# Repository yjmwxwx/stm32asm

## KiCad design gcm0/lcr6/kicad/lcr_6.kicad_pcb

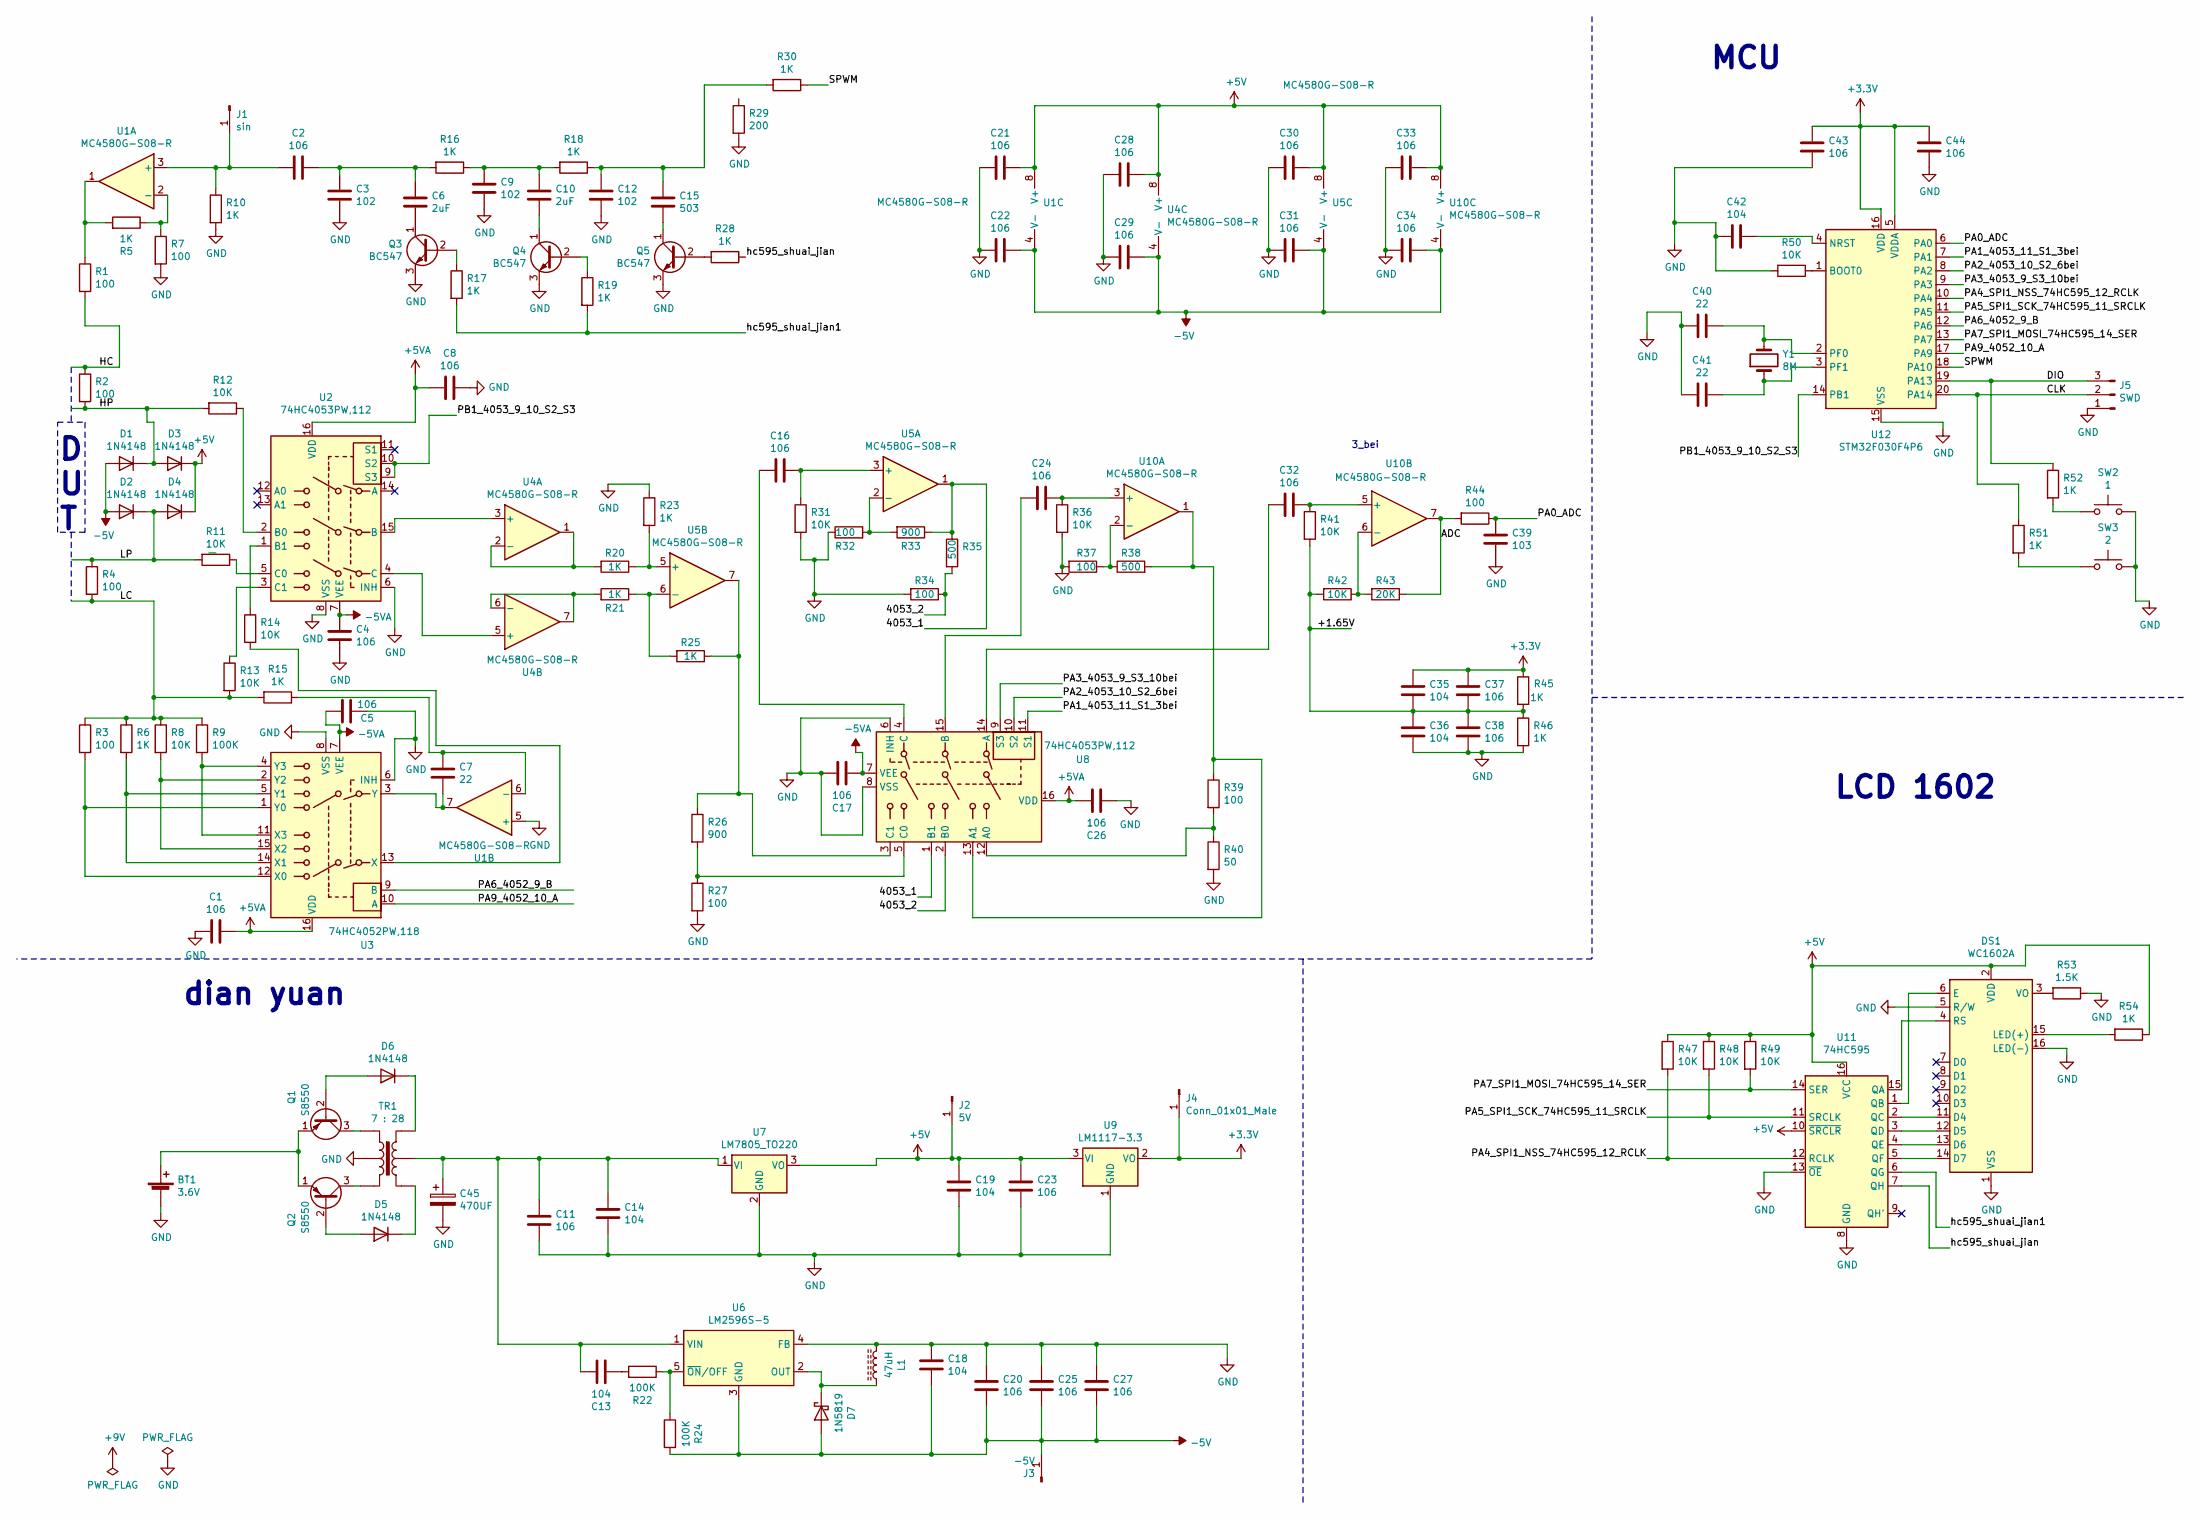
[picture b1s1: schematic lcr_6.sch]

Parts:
BT1: 3.6V; PinHeader_1x02_P2.54mm_Vertical
C1, C2, C4, C5, C8, C11, C16, C17, C20, C21, C22, C23, C24, C25, C26, C27, C28, C29, C30, C31, C32, C33, C34, C37, C38, C43, C44: 106; C_0805_2012Metric_Pad1.18x1.45mm_HandSolder
C3, C9, C12: 102; C_0805_2012Metric_Pad1.18x1.45mm_HandSolder
C6, C10: 2uF; C_0805_2012Metric_Pad1.18x1.45mm_HandSolder
C7, C40, C41: 22; C_0805_2012Metric_Pad1.18x1.45mm_HandSolder
C13, C14, C18, C19, C35, C36, C42: 104; C_0805_2012Metric_Pad1.18x1.45mm_HandSolder
C15: 503; C_0805_2012Metric_Pad1.18x1.45mm_HandSolder
C39: 103; C_0805_2012Metric_Pad1.18x1.45mm_HandSolder
C45: 470UF; CP_Radial_D8.0mm_P3.80mm
D1, D2, D3, D4: 1N4148; D_SMA
D5, D6: 1N4148; D_DO-35_SOD27_P7.62mm_Horizontal
D7: 1N5819; D_SMA
DS1: WC1602A; PinHeader_1x16_P2.54mm_Vertical
J1: sin; PinHeader_1x01_P2.54mm_Vertical
J2: 5V; PinHeader_1x01_P2.54mm_Vertical
J3: -5V; PinHeader_1x01_P2.54mm_Vertical
J4: Conn_01x01_Male; PinHeader_1x01_P2.54mm_Vertical
J5: SWD; PinHeader_1x03_P2.54mm_Vertical
L1: 47uH; L_Radial_D6.0mm_P4.00mm
Q1, Q2: S8550; TO-92_Inline
Q3, Q4, Q5: BC547; TO-92_Inline
R1, R2, R3, R4, R7, R27, R32, R34, R37, R39, R44: 100; R_0805_2012Metric_Pad1.20x1.40mm_HandSolder
R5, R6, R10, R15, R16, R17, R18, R19, R20, R21, R23, R25, R28, R30, R45, R46, R51, R52, R54: 1K; R_0805_2012Metric_Pad1.20x1.40mm_HandSolder
R8, R11, R12, R13, R14, R31, R36, R41, R42, R47, R48, R49, R50: 10K; R_0805_2012Metric_Pad1.20x1.40mm_HandSolder
R9, R22, R24: 100K; R_0805_2012Metric_Pad1.20x1.40mm_HandSolder
R26, R33: 900; R_0805_2012Metric_Pad1.20x1.40mm_HandSolder
R29: 200; R_0805_2012Metric_Pad1.20x1.40mm_HandSolder
R35, R38: 500; R_0805_2012Metric_Pad1.20x1.40mm_HandSolder
R40: 50; R_0805_2012Metric_Pad1.20x1.40mm_HandSolder
R43: 20K; R_0805_2012Metric_Pad1.20x1.40mm_HandSolder
R53: 1.5K; R_0805_2012Metric_Pad1.20x1.40mm_HandSolder
SW2: 1; SW_Tactile_SPST_Angled_PTS645Vx58-2LFS
SW3: 2; SW_Tactile_SPST_Angled_PTS645Vx58-2LFS
TR1: 7 : 28; Transformer_Toroid_Tapped_Horizontal_D9.0mm_Amidon-T30
U1, U4, U5, U10: MC4580G-S08-R; SOP-8_3.9x4.9mm_P1.27mm
U2, U8: 74HC4053PW,112; TSSOP-16_4.4x5mm_P0.65mm
U3: 74HC4052PW,118; TSSOP-16_4.4x5mm_P0.65mm
U6: LM2596S-5; TO-263-5_TabPin3
U7: LM7805_TO220; TO-263-2
U9: LM1117-3.3; SOT-223-3_TabPin2
U11: 74HC595; TSSOP-16_4.4x5mm_P0.65mm
U12: STM32F030F4P6; TSSOP-20_4.4x6.5mm_P0.65mm
Y1: 8M; Crystal_HC49-4H_Vertical

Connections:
+3V3: C35.1, C37.1, C43.1, C44.1, J4.1, R45.1, U9.2 (VO), U12.5 (VDDA), U12.16 (VDD)
+5V: C19.1, C21.1, C23.1, C28.1, C30.1, C33.1, D3.1 (K), D4.1 (K), DS1.2 (VDD), J2.1, R47.1, R48.1, R49.1, R54.1, U1.8 (V+), U4.8 (V+), U5.8 (V+), U7.3 (VO), U9.3 (VI), U10.8 (V+), U11.10 (~SRCLR), U11.16 (VCC); also elsewhere on the board
+5VA: C1.1, C8.2, C26.2, U2.16 (VDD), U3.16 (VDD), U8.16 (VDD)
-5V: C18.2, C20.2, C22.1, C25.2, C27.2, C29.1, C31.1, C34.1, D1.2 (A), D2.2 (A), D7.2 (A), J3.1, R24.2, U1.4 (V-), U4.4 (V-), U5.4 (V-), U6.3 (GND), U10.4 (V-); also elsewhere on the board
-5VA: C4.1, C5.2, C17.1, U2.7 (VEE), U3.7 (VEE), U8.7 (VEE)
/4053_1: R33.1, R35.1, U5.1, U8.1 (B1)
/4053_2: R34.1, R35.2, U8.2 (B0)
/+1.65V: C35.2, C36.1, C37.2, C38.1, R41.2, R42.2, R45.2, R46.1
/ADC: R43.1, R44.2, U10.7
/CLK: J5.2, R51.1, U12.20 (PA14)
/DIO: J5.3, R52.1, U12.19 (PA13)
/HC: R1.2, R2.1
/HP: D1.1 (K), D3.2 (A), R2.2, R12.2
/LC: R3.1, R4.2, R6.1, R8.1, R9.1, R13.2, R15.2
/LP: D2.1 (K), D4.2 (A), R4.1, R11.2
/PA0_ADC: C39.1, R44.1, U12.6 (PA0)
/PA1_4053_11_S1_3bei: U8.11 (S1), U12.7 (PA1)
/PA2_4053_10_S2_6bei: U8.10 (S2), U12.8 (PA2)
/PA3_4053_9_S3_10bei: U8.9 (S3), U12.9 (PA3)
/PA4_SPI1_NSS_74HC595_12_RCLK: R47.2, U11.12 (RCLK), U12.10 (PA4)
/PA5_SPI1_SCK_74HC595_11_SRCLK: R48.2, U11.11 (SRCLK), U12.11 (PA5)
/PA6_4052_9_B: U3.9 (B), U12.12 (PA6)
/PA7_SPI1_MOSI_74HC595_14_SER: R49.2, U11.14 (SER), U12.13 (PA7)
/PA9_4052_10_A: U3.10 (A), U12.17 (PA9)
/PB1_4053_9_10_S2_S3: U2.9 (S3), U2.10 (S2), U12.14 (PB1)
/SPWM: R30.1, U12.18 (PA10)
/hc595_shuai_jian: R28.1, U11.7 (QH)
/hc595_shuai_jian1: R17.2, R19.2, U11.6 (QG)
GND: BT1.2 (-), C1.2, C3.2, C4.2, C5.1, C8.1, C9.2, C11.2, C12.2, C14.2, C17.2, C18.1, C19.2, C20.1, C21.2, C22.2, C23.2, C25.1, C26.1, C27.1, C28.2, C29.2, C30.2, C31.2, C33.2, C34.2, C36.2, C38.2, C39.2, C40.1, C41.2, C42.2, C43.2, C44.2, C45.2, DS1.1 (VSS), DS1.5 (R/W), DS1.16 (LED(-)), J5.1, L1.1, Q3.3 (E), Q4.3 (E), Q5.3 (E), R7.2, R10.2, R23.1, R27.2, R29.2, R31.2, R32.1, R34.2, R36.2, R37.2, R40.2, R46.2, R50.2, R53.1, SW2.2, SW3.2, TR1.2, U1.5 (+), U2.6 (INH), U2.8 (VSS), U3.6 (INH), U3.8 (VSS), U6.4 (FB), U7.2 (GND), U8.6 (INH), U8.8 (VSS), U9.1 (GND), U11.8 (GND), U11.13 (~OE), U12.15 (VSS)
unnamed: BT1.1 (+), Q1.1 (E), Q2.1 (E)
unnamed: C2.1, C3.1, C6.1, R16.2
unnamed 31: C2.2, J1.1, R10.1, U1.3 (+); also elsewhere on the board
unnamed: C6.2, Q3.1 (C)
unnamed: C7.1, R15.1, U1.6 (-)
unnamed: C7.2, U1.7, U3.3 (Y)
unnamed: C9.1, C10.1, R16.1, R18.2
unnamed: C10.2, Q4.1 (C)
unnamed: C11.1, C13.2, C14.1, C45.1, TR1.5, U6.1 (VIN), U7.1 (VI)
unnamed: C12.1, C15.1, R18.1, R30.2
unnamed: C13.1, R22.2
unnamed: C15.2, Q5.1 (C)
unnamed: C16.1, R31.1, U5.3 (+)
unnamed: C16.2, U8.4 (C)
unnamed: C24.1, R36.1, U10.3 (+)
unnamed: C24.2, U8.15 (B)
unnamed: C32.1, R41.1, U10.5 (+)
unnamed: C32.2, U8.14 (A)
unnamed: C40.2, U12.2 (PF0), Y1.2
unnamed: C41.1, U12.3 (PF1), Y1.1
unnamed: C42.1, U12.4 (NRST)
unnamed: D5.1 (K), TR1.4
unnamed: D5.2 (A), Q2.2 (B)
unnamed: D6.1 (K), TR1.6
unnamed: D6.2 (A), Q1.2 (B)
unnamed: D7.1 (K), L1.2, U6.2 (OUT)
unnamed: DS1.3 (VO), R53.2
unnamed: DS1.4 (RS), U11.15 (QA)
unnamed: DS1.6 (E), U11.1 (QB)
unnamed: DS1.11 (D4), U11.2 (QC)
unnamed: DS1.12 (D5), U11.3 (QD)
unnamed: DS1.13 (D6), U11.4 (QE)
unnamed: DS1.14 (D7), U11.5 (QF)
unnamed: DS1.15 (LED(+)), R54.2
unnamed: Q1.3 (C), TR1.1
unnamed: Q2.3 (C), TR1.3
unnamed: Q3.2 (B), R17.1
unnamed: Q4.2 (B), R19.1
unnamed: Q5.2 (B), R28.2
unnamed: R1.1, R5.2, U1.1
unnamed: R3.2, U3.1 (Y0), U3.12 (X0)
unnamed: R5.1, R7.1, U1.2 (-)
unnamed: R6.2, U3.5 (Y1), U3.14 (X1)
unnamed: R8.2, U3.2 (Y2), U3.15 (X2)
unnamed: R9.2, U3.4 (Y3), U3.11 (X3)
unnamed: R11.1, U2.5 (C0)
unnamed: R12.1, U2.2 (B0)
unnamed: R13.1, U2.3 (C1)
unnamed: R14.1, U2.1 (B1)
unnamed: R14.2, U3.13 (X)
unnamed: R20.1, R23.2, U5.5 (+)
unnamed: R20.2, U4.1, U4.2 (-)
unnamed: R21.1, R25.2, U5.6 (-)
unnamed: R21.2, U4.6 (-), U4.7
unnamed: R22.1, R24.1, U6.5 (~ON~/OFF)
unnamed: R25.1, R26.1, U5.7, U8.3 (C1)
unnamed: R26.2, R27.1, U8.5 (C0)
unnamed: R32.2, R33.2, U5.2 (-)
unnamed: R37.1, R38.1, U10.2 (-)
unnamed: R38.2, R39.1, U8.13 (A1), U10.1
unnamed: R39.2, R40.1, U8.12 (A0)
unnamed: R42.1, R43.2, U10.6 (-)
unnamed: R50.1, U12.1 (BOOT0)
unnamed: R51.2, SW3.1
unnamed: R52.2, SW2.1
unnamed: U2.4 (C), U4.5 (+)
unnamed: U2.15 (B), U4.3 (+)

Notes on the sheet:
D U T
LCD 1602
MCU
3_bei
dian yuan

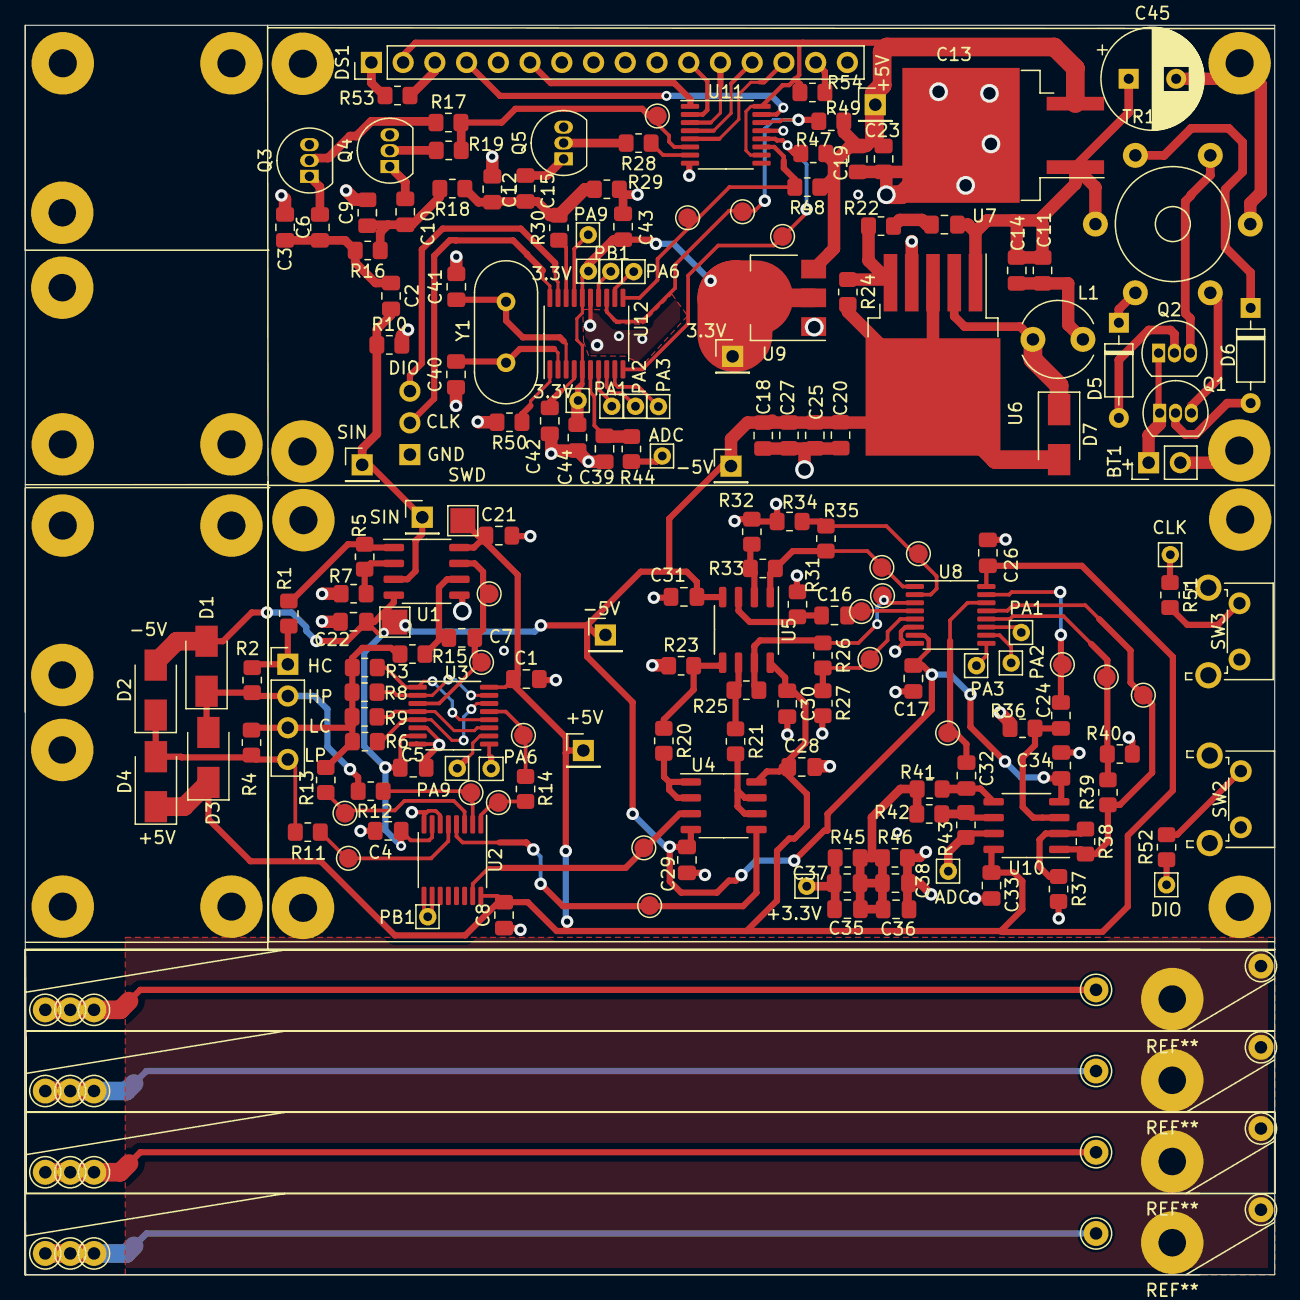
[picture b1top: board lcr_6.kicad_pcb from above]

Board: 2 copper layers, 100.0 x 100.0 mm, 138 parts (1 on the bottom side), 96 nets.

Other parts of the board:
J1#2: sin; PinHeader_1x01_P2.54mm_Vertical
J2#2: 5V; PinHeader_1x01_P2.54mm_Vertical
J3#2: -5V; PinHeader_1x01_P2.54mm_Vertical

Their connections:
+5V: J2#2.1; also elsewhere on the board
-5V: J3#2.1; also elsewhere on the board
unnamed 31: J1#2.1; also elsewhere on the board

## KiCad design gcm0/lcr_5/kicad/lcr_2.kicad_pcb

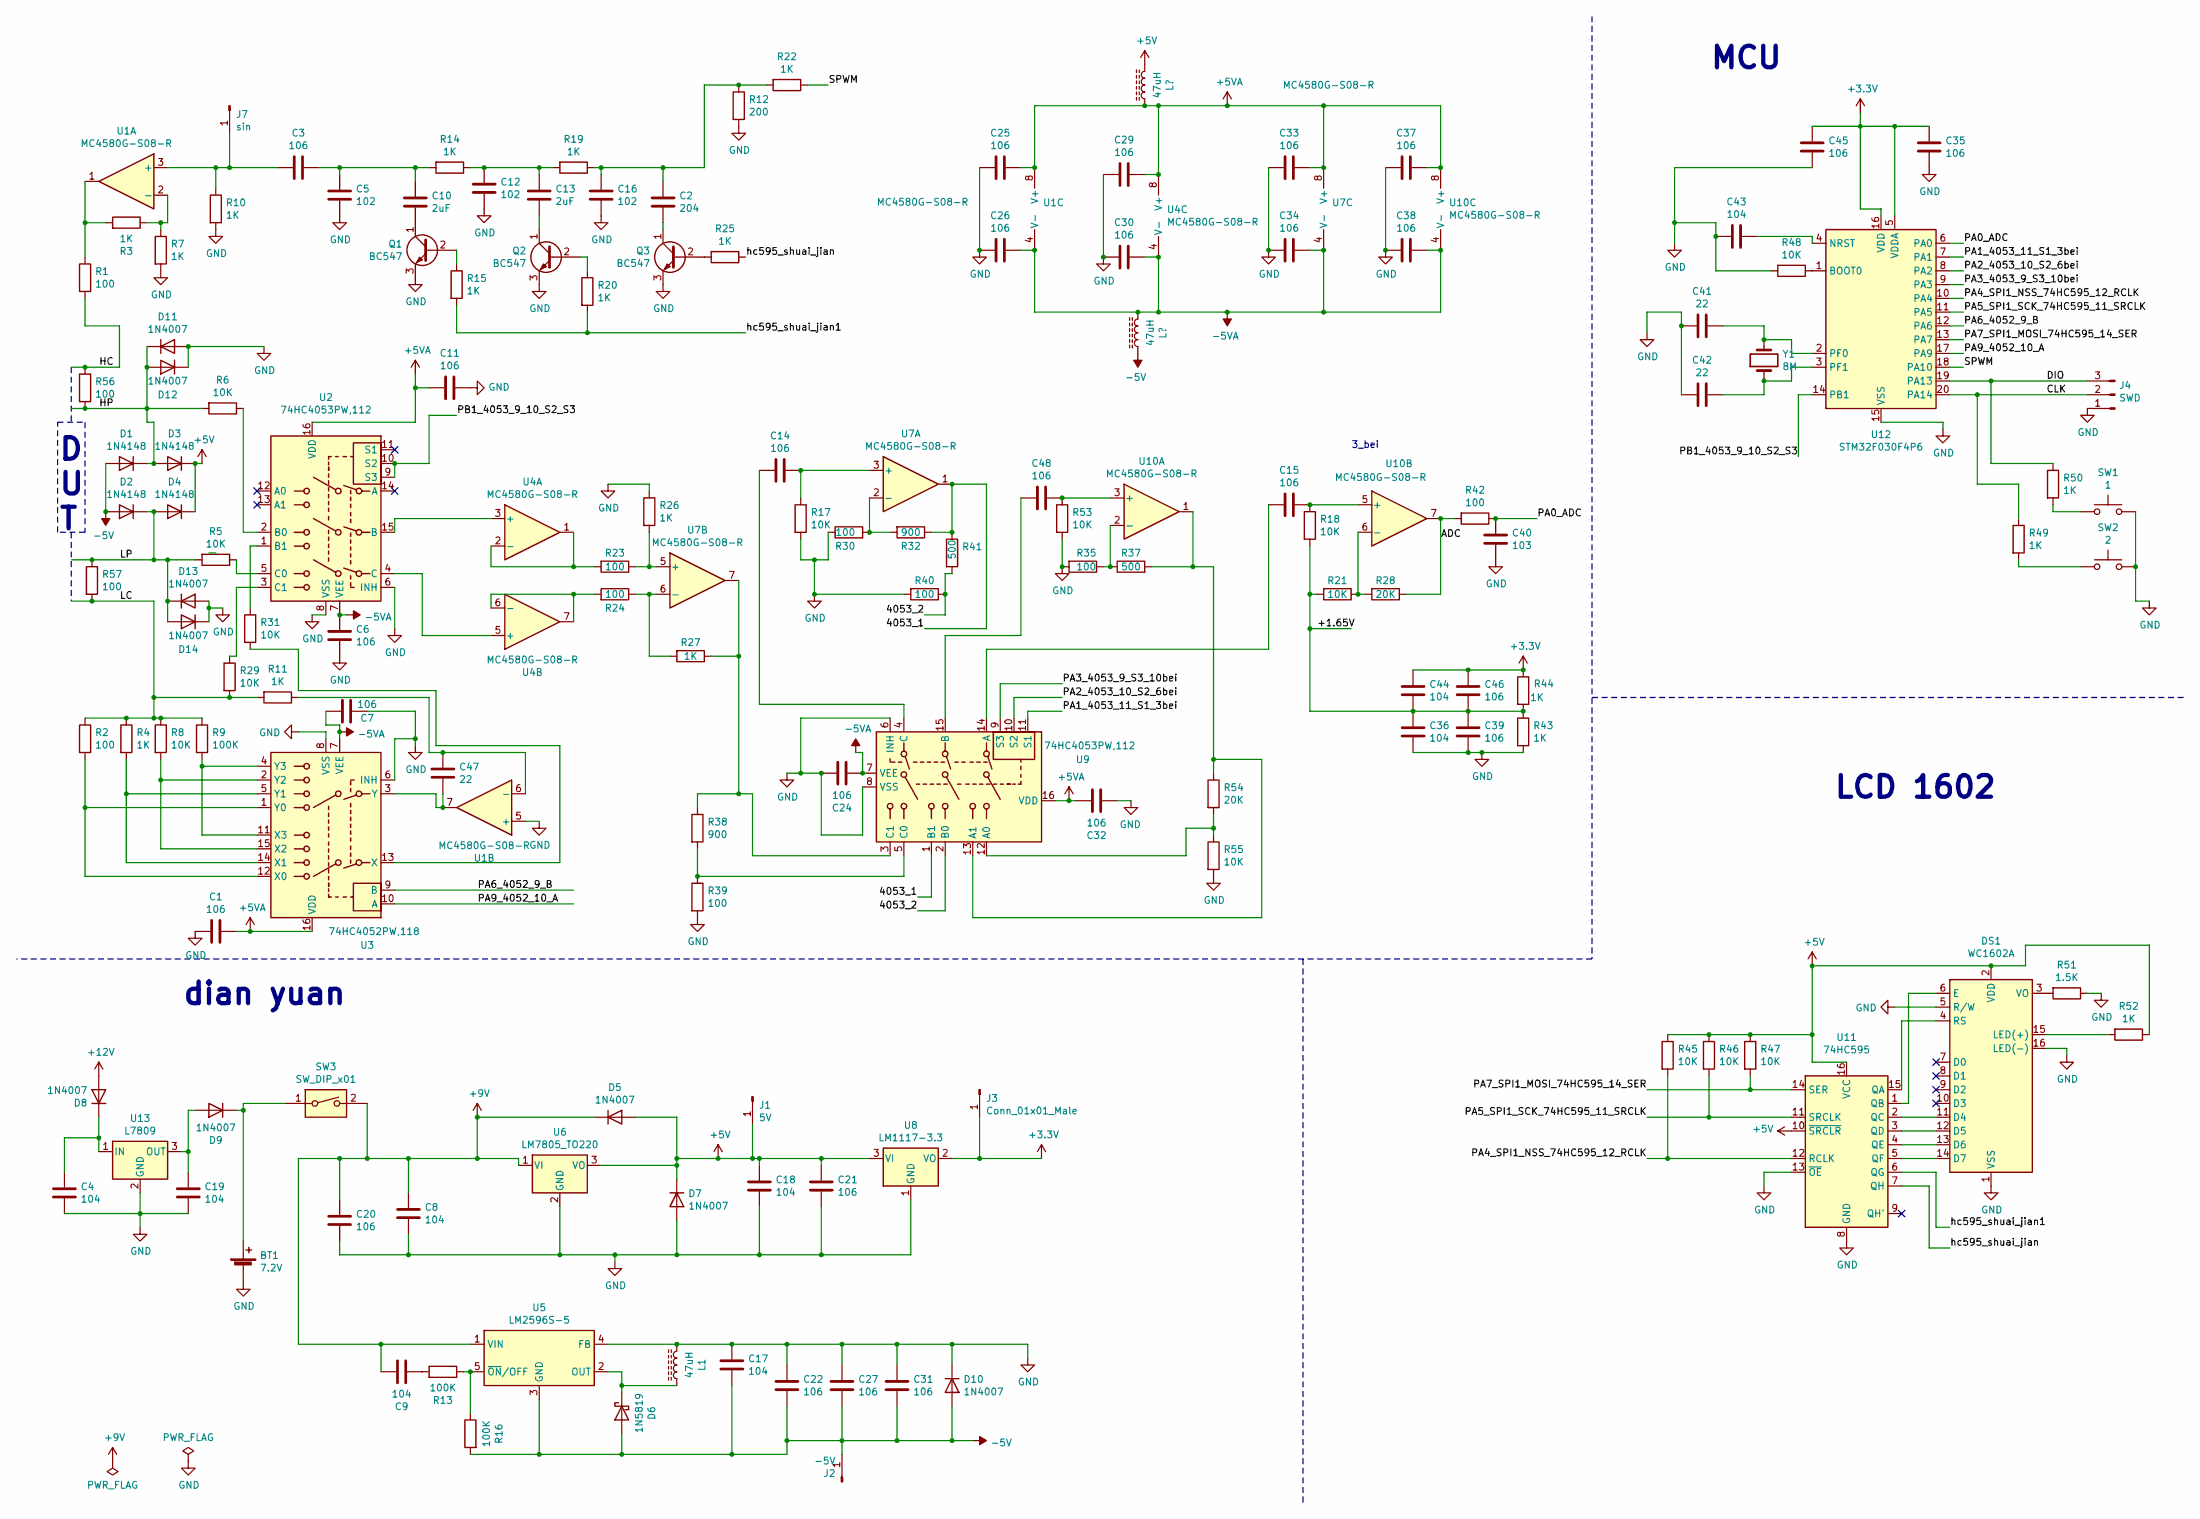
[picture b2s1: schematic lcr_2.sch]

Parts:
BT1: 7.2V; PinHeader_1x02_P2.54mm_Vertical
C1, C3, C6, C7, C11, C14, C15, C20, C21, C22, C24, C25, C26, C27, C29, C30, C31, C32, C33, C34, C35, C37, C38, C39, C45, C46, C48: 106; C_0805_2012Metric_Pad1.18x1.45mm_HandSolder
C2: 204; C_0805_2012Metric_Pad1.18x1.45mm_HandSolder
C4, C8, C9, C17, C18, C19, C36, C43, C44: 104; C_0805_2012Metric_Pad1.18x1.45mm_HandSolder
C5, C12, C16: 102; C_0805_2012Metric_Pad1.18x1.45mm_HandSolder
C10, C13: 2uF; C_0805_2012Metric_Pad1.18x1.45mm_HandSolder
C40: 103; C_0805_2012Metric_Pad1.18x1.45mm_HandSolder
C41, C42, C47: 22; C_0805_2012Metric_Pad1.18x1.45mm_HandSolder
D1, D2, D3, D4: 1N4148; D_SMA
D5, D7, D8, D9, D10, D11, D12, D13, D14: 1N4007; D_DO-41_SOD81_P2.54mm_Vertical_AnodeUp
D6: 1N5819; D_SMA
DS1: WC1602A; PinHeader_1x16_P2.54mm_Vertical
J1: 5V; PinHeader_1x01_P2.54mm_Vertical
J2: -5V; PinHeader_1x01_P2.54mm_Vertical
J3: Conn_01x01_Male; PinHeader_1x01_P2.54mm_Vertical
J4: SWD; PinHeader_1x03_P2.54mm_Vertical
J7: sin; PinHeader_1x01_P2.54mm_Vertical
L1: 47uH; L_Radial_D6.0mm_P4.00mm
Q1, Q2, Q3: BC547; TO-92_Inline
R1, R2, R23, R24, R30, R35, R39, R40, R42, R56, R57: 100; R_0805_2012Metric_Pad1.20x1.40mm_HandSolder
R3, R4, R7, R10, R11, R14, R15, R19, R20, R22, R25, R26, R27, R43, R44, R49, R50, R52: 1K; R_0805_2012Metric_Pad1.20x1.40mm_HandSolder
R5, R6, R8, R17, R18, R21, R29, R31, R45, R46, R47, R48, R53, R55: 10K; R_0805_2012Metric_Pad1.20x1.40mm_HandSolder
R9, R13, R16: 100K; R_0805_2012Metric_Pad1.20x1.40mm_HandSolder
R12: 200; R_0805_2012Metric_Pad1.20x1.40mm_HandSolder
R28, R54: 20K; R_0805_2012Metric_Pad1.20x1.40mm_HandSolder
R32, R38: 900; R_0805_2012Metric_Pad1.20x1.40mm_HandSolder
R37, R41: 500; R_0805_2012Metric_Pad1.20x1.40mm_HandSolder
R51: 1.5K; R_0805_2012Metric_Pad1.20x1.40mm_HandSolder
SW1: 1; SW_Tactile_SPST_Angled_PTS645Vx58-2LFS
SW2: 2; SW_Tactile_SPST_Angled_PTS645Vx58-2LFS
SW3: SW_DIP_x01; PinHeader_1x02_P2.54mm_Vertical
U1, U4, U7, U10: MC4580G-S08-R; SOP-8_3.9x4.9mm_P1.27mm
U2, U9: 74HC4053PW,112; TSSOP-16_4.4x5mm_P0.65mm
U3: 74HC4052PW,118; TSSOP-16_4.4x5mm_P0.65mm
U5: LM2596S-5; TO-263-5_TabPin3
U6: LM7805_TO220; TO-263-2
U8: LM1117-3.3; SOT-223-3_TabPin2
U11: 74HC595; TSSOP-16_4.4x5mm_P0.65mm
U12: STM32F030F4P6; TSSOP-20_4.4x6.5mm_P0.65mm
U13: L7809; TO-263-2
Y1: 8M; Crystal_HC49-4H_Vertical

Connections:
+3V3: C35.1, C44.1, C45.1, C46.1, J3.1, R44.1, U8.2 (VO), U12.5 (VDDA), U12.16 (VDD)
+9V: C8.1, C9.2, C20.1, D5.1 (K), SW3.2, U5.1 (VIN), U6.1 (VI)
+12V: D8.2 (A)
/4053_1: R32.1, R41.1, U7.1, U9.1 (B1)
/4053_2: R40.1, R41.2, U9.2 (B0)
/+1.65V: C36.1, C39.1, C44.2, C46.2, R18.2, R21.2, R43.1, R44.2
/ADC: R28.1, R42.2, U10.7
/CLK: J4.2, R49.1, U12.20 (PA14)
/DIO: J4.3, R50.1, U12.19 (PA13)
/HC: R1.2, R56.1
/HP: D1.1 (K), D3.2 (A), D11.1 (K), D12.2 (A), R6.2, R56.2
/LC: R2.1, R4.1, R8.1, R9.1, R11.2, R29.2, R57.2
/LP: D2.1 (K), D4.2 (A), D13.1 (K), D14.2 (A), R5.2, R57.1
/PA0_ADC: C40.1, R42.1, U12.6 (PA0)
/PA1_4053_11_S1_3bei: U9.11 (S1), U12.7 (PA1)
/PA2_4053_10_S2_6bei: U9.10 (S2), U12.8 (PA2)
/PA3_4053_9_S3_10bei: U9.9 (S3), U12.9 (PA3)
/PA4_SPI1_NSS_74HC595_12_RCLK: R45.2, U11.12 (RCLK), U12.10 (PA4)
/PA5_SPI1_SCK_74HC595_11_SRCLK: R46.2, U11.11 (SRCLK), U12.11 (PA5)
/PA6_4052_9_B: U3.9 (B), U12.12 (PA6)
/PA7_SPI1_MOSI_74HC595_14_SER: R47.2, U11.14 (SER), U12.13 (PA7)
/PA9_4052_10_A: U3.10 (A), U12.17 (PA9)
/PB1_4053_9_10_S2_S3: U2.9 (S3), U2.10 (S2), U12.14 (PB1)
/SPWM: R22.1, U12.18 (PA10)
/hc595_shuai_jian: R25.1, U11.7 (QH)
/hc595_shuai_jian1: R15.2, R20.2, U11.6 (QG)
GND: BT1.2 (-), C1.2, C4.2, C5.2, C6.2, C7.1, C8.2, C11.1, C12.2, C16.2, C17.1, C18.2, C19.2, C20.2, C21.2, C22.1, C24.2, C25.2, C26.2, C27.1, C29.2, C30.2, C31.1, C32.1, C33.2, C34.2, C35.2, C36.2, C37.2, C38.2, C39.2, C40.2, C41.1, C42.2, C43.2, C45.2, D7.2 (A), D10.1 (K), D11.2 (A), D12.1 (K), D13.2 (A), D14.1 (K), DS1.1 (VSS), DS1.5 (R/W), DS1.16 (LED(-)), J4.1, L1.1, Q1.3 (E), Q2.3 (E), Q3.3 (E), R7.2, R10.2, R12.2, R17.2, R26.1, R30.1, R35.2, R39.2, R40.2, R43.2, R48.2, R51.1, R53.2, R55.2, SW1.2, SW2.2, U1.5 (+), U2.6 (INH), U2.8 (VSS), U3.6 (INH), U3.8 (VSS), U5.4 (FB), U6.2 (GND), U8.1 (GND), U9.6 (INH), U9.8 (VSS), U11.8 (GND), U11.13 (~OE), U12.15 (VSS), U13.2 (GND)
unnamed: BT1.1 (+), D9.1 (K), SW3.1
unnamed: C2.2, Q3.1 (C)
unnamed 29: C3.2, J7.1, R10.1, U1.3 (+); also elsewhere on the board
unnamed: C4.1, D8.1 (K), U13.1 (IN)
unnamed: C9.1, R13.2
unnamed: C3.1, C5.1, C10.1, R14.2
unnamed: C10.2, Q1.1 (C)
unnamed: C12.1, C13.1, R14.1, R19.2
unnamed: C13.2, Q2.1 (C)
unnamed: C14.1, R17.1, U7.3 (+)
unnamed: C14.2, U9.4 (C)
unnamed: C15.1, R18.1, U10.5 (+)
unnamed: C15.2, U9.14 (A)
unnamed: C2.1, C16.1, R12.1, R19.1, R22.2
unnamed: C19.1, D9.2 (A), U13.3 (OUT)
unnamed: C41.2, U12.2 (PF0), Y1.2
unnamed: C42.1, U12.3 (PF1), Y1.1
unnamed: C43.1, U12.4 (NRST)
unnamed: C47.1, R11.1, U1.6 (-)
unnamed: C47.2, U1.7, U3.3 (Y)
unnamed: C48.1, R53.1, U10.3 (+)
unnamed: C48.2, U9.15 (B)
unnamed: D6.1 (K), L1.2, U5.2 (OUT)
unnamed: DS1.3 (VO), R51.2
unnamed: DS1.4 (RS), U11.15 (QA)
unnamed: DS1.6 (E), U11.1 (QB)
unnamed: DS1.11 (D4), U11.2 (QC)
unnamed: DS1.12 (D5), U11.3 (QD)
unnamed: DS1.13 (D6), U11.4 (QE)
unnamed: DS1.14 (D7), U11.5 (QF)
unnamed: DS1.15 (LED(+)), R52.2
unnamed: Q1.2 (B), R15.1
unnamed: Q2.2 (B), R20.1
unnamed: Q3.2 (B), R25.2
unnamed: R1.1, R3.2, U1.1
unnamed: R2.2, U3.1 (Y0), U3.12 (X0)
unnamed: R3.1, R7.1, U1.2 (-)
unnamed: R4.2, U3.5 (Y1), U3.14 (X1)
unnamed: R5.1, U2.5 (C0)
unnamed: R6.1, U2.2 (B0)
unnamed: R8.2, U3.2 (Y2), U3.15 (X2)
unnamed: R9.2, U3.4 (Y3), U3.11 (X3)
unnamed: R13.1, R16.1, U5.5 (~ON~/OFF)
unnamed: R21.1, R28.2, U10.6 (-)
unnamed: R23.1, R26.2, U7.5 (+)
unnamed: R24.1, R27.2, U7.6 (-)
unnamed: R27.1, R38.1, U7.7, U9.3 (C1)
unnamed: R29.1, U2.3 (C1)
unnamed: R30.2, R32.2, U7.2 (-)
unnamed: R31.1, U2.1 (B1)
unnamed: R31.2, U3.13 (X)
unnamed: R35.1, R37.1, U10.2 (-)
unnamed: R37.2, R54.1, U9.13 (A1), U10.1
unnamed: R38.2, R39.1, U9.5 (C0)
unnamed: R48.1, U12.1 (BOOT0)
unnamed: R49.2, SW2.1
unnamed: R50.2, SW1.1
unnamed: R54.2, R55.1, U9.12 (A0)
unnamed: U2.4 (C), U4.5 (+)
unnamed: U2.15 (B), U4.3 (+)

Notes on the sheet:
D U T
LCD 1602
MCU
dian yuan
3_bei

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
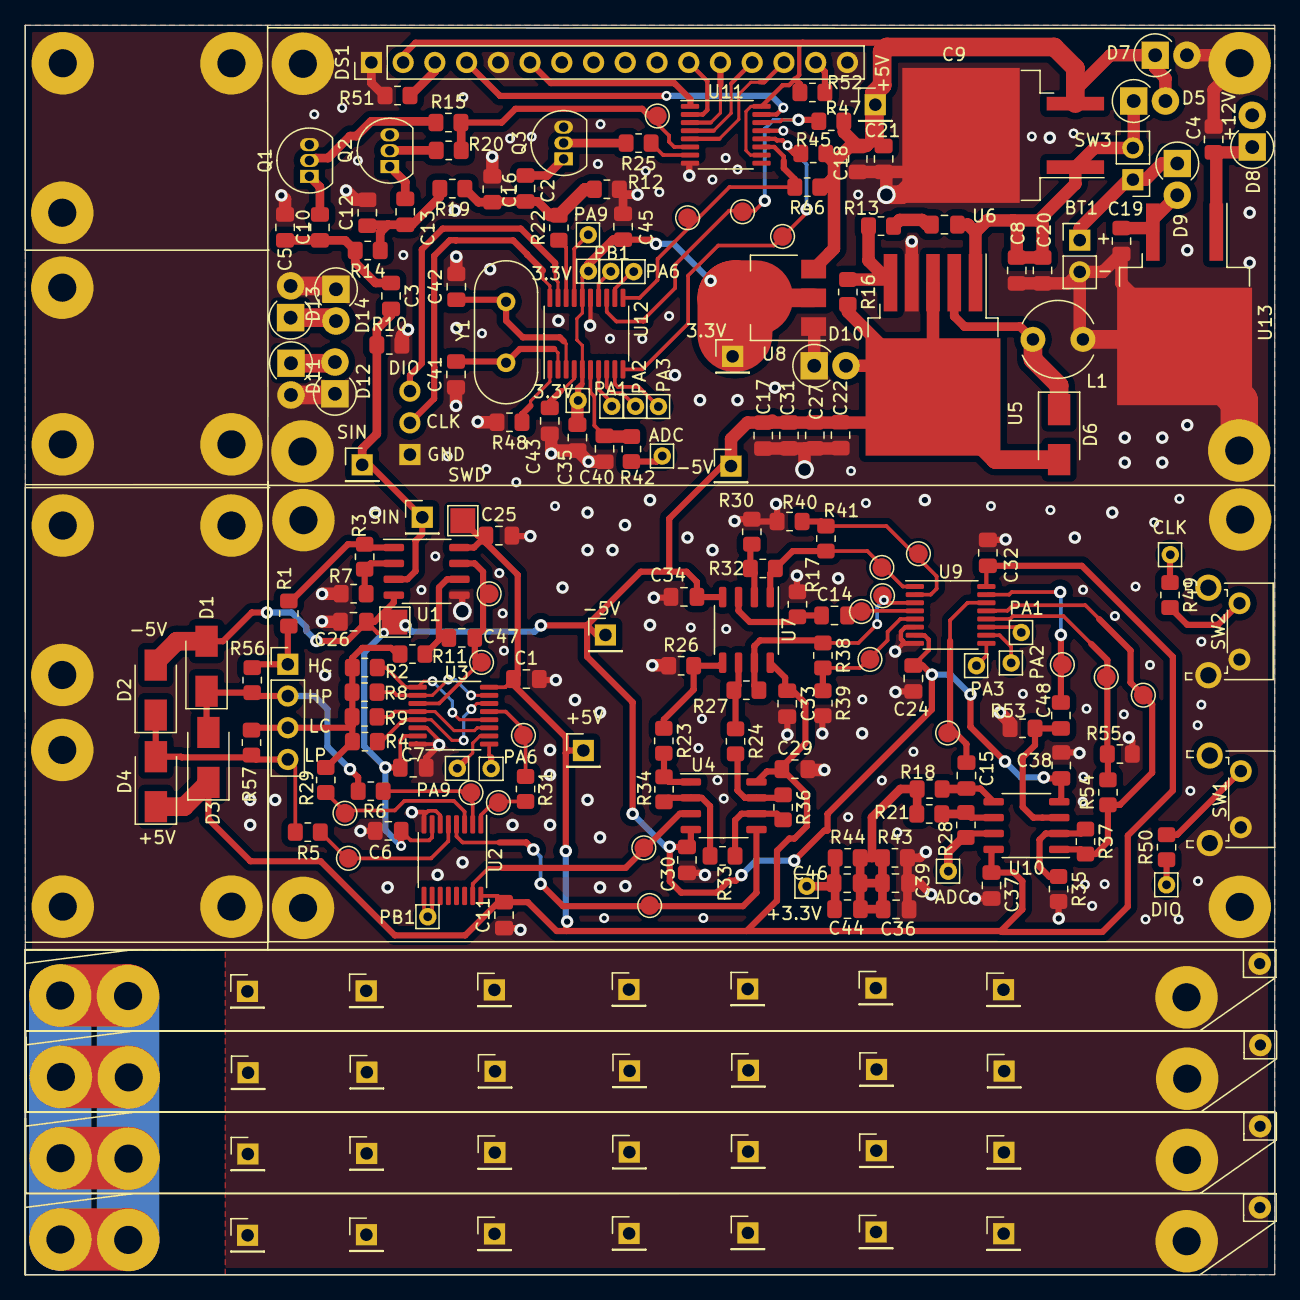
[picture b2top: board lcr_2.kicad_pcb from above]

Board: 2 copper layers, 100.0 x 100.0 mm, 148 parts (1 on the bottom side), 92 nets.

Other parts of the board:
J1#2: 5V; PinHeader_1x01_P2.54mm_Vertical
J2#2: -5V; PinHeader_1x01_P2.54mm_Vertical
J7#2: sin; PinHeader_1x01_P2.54mm_Vertical
R33: 100; R_0805_2012Metric_Pad1.20x1.40mm_HandSolder
R34, R36: 1K; R_0805_2012Metric_Pad1.20x1.40mm_HandSolder

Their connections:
unnamed 29: J7#2.1; also elsewhere on the board
